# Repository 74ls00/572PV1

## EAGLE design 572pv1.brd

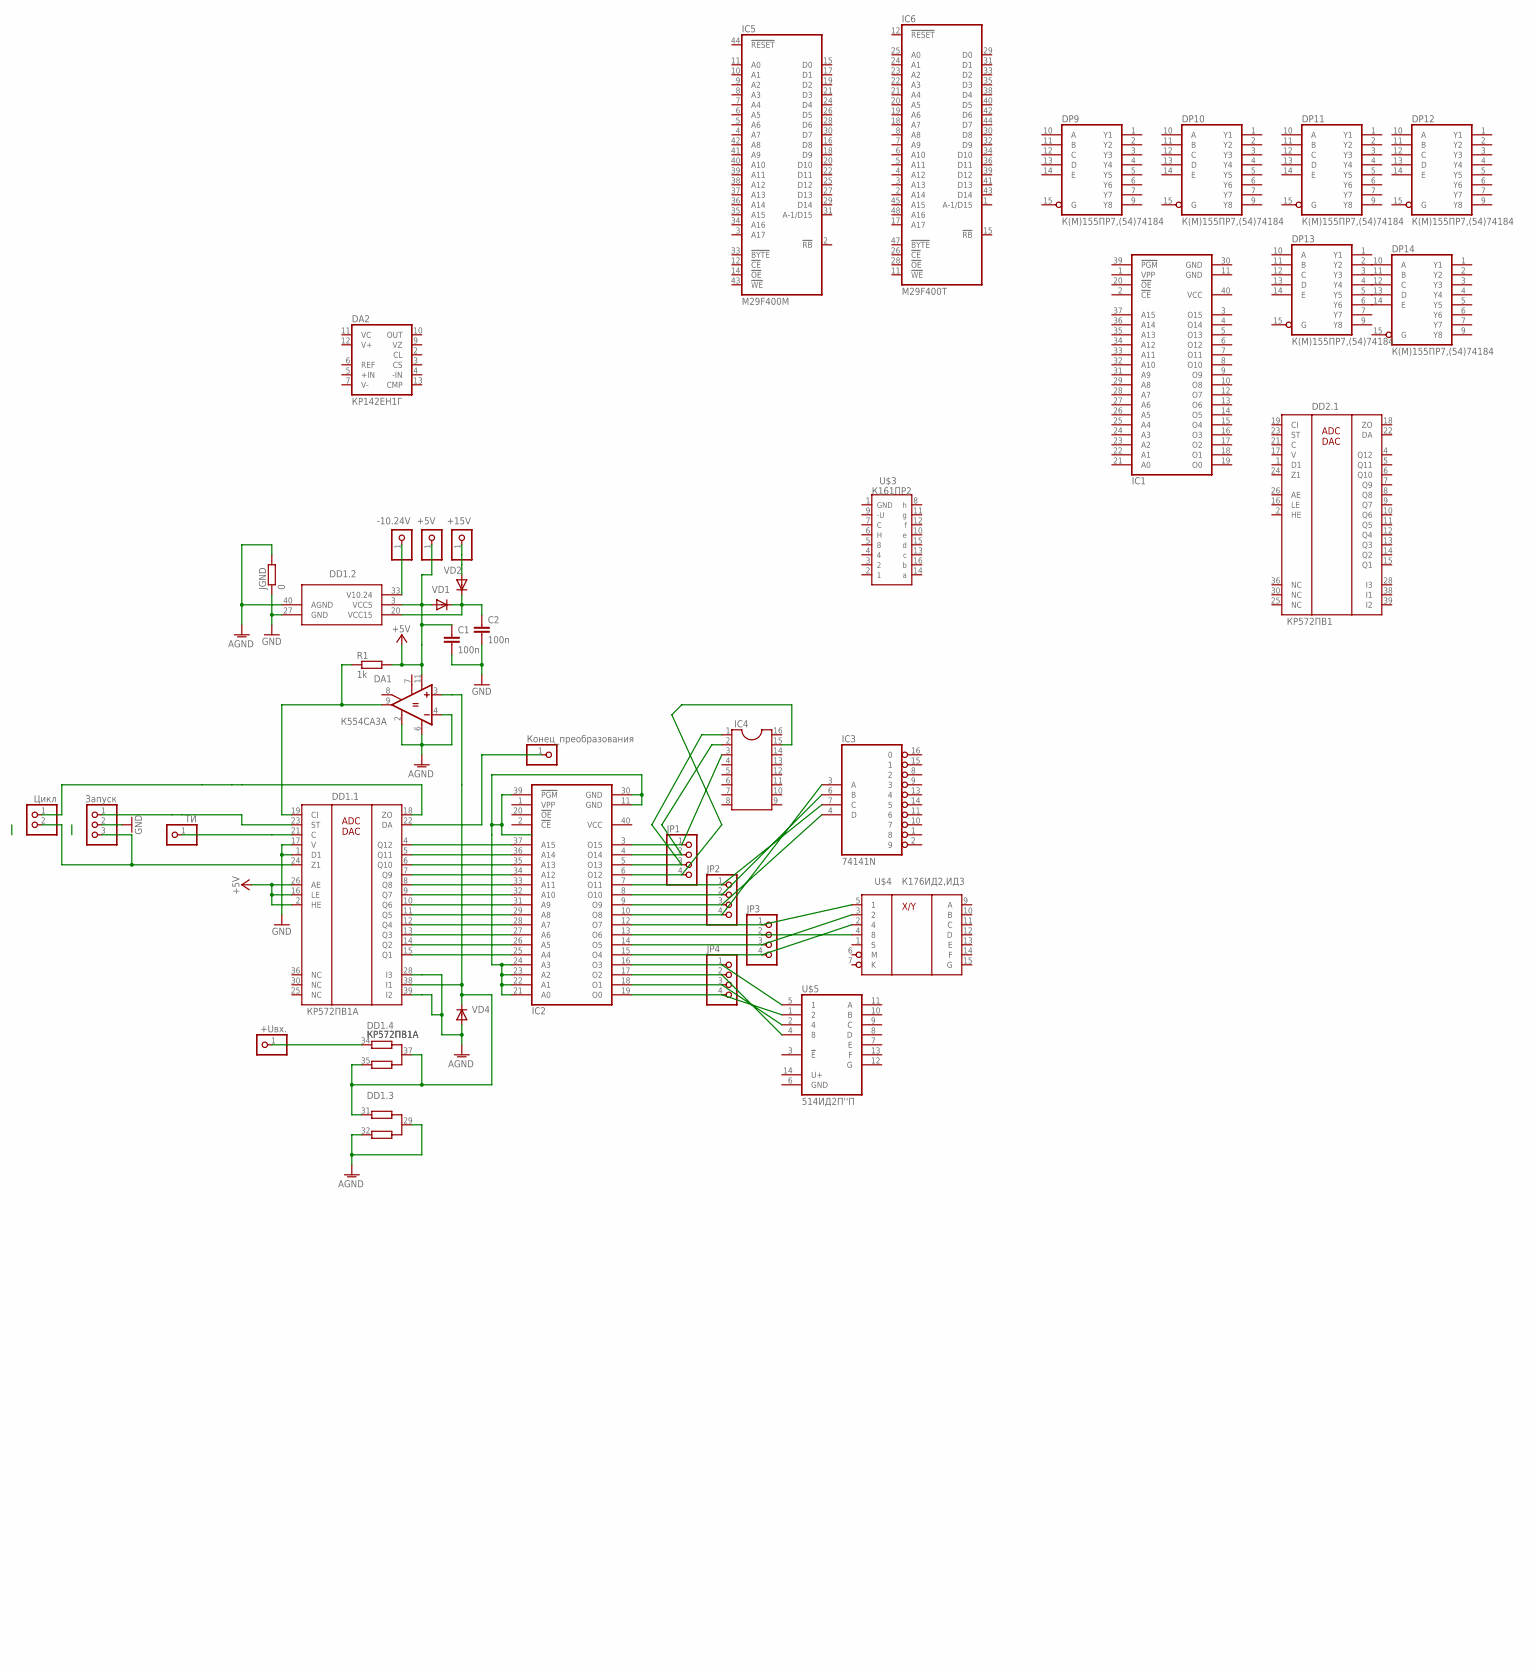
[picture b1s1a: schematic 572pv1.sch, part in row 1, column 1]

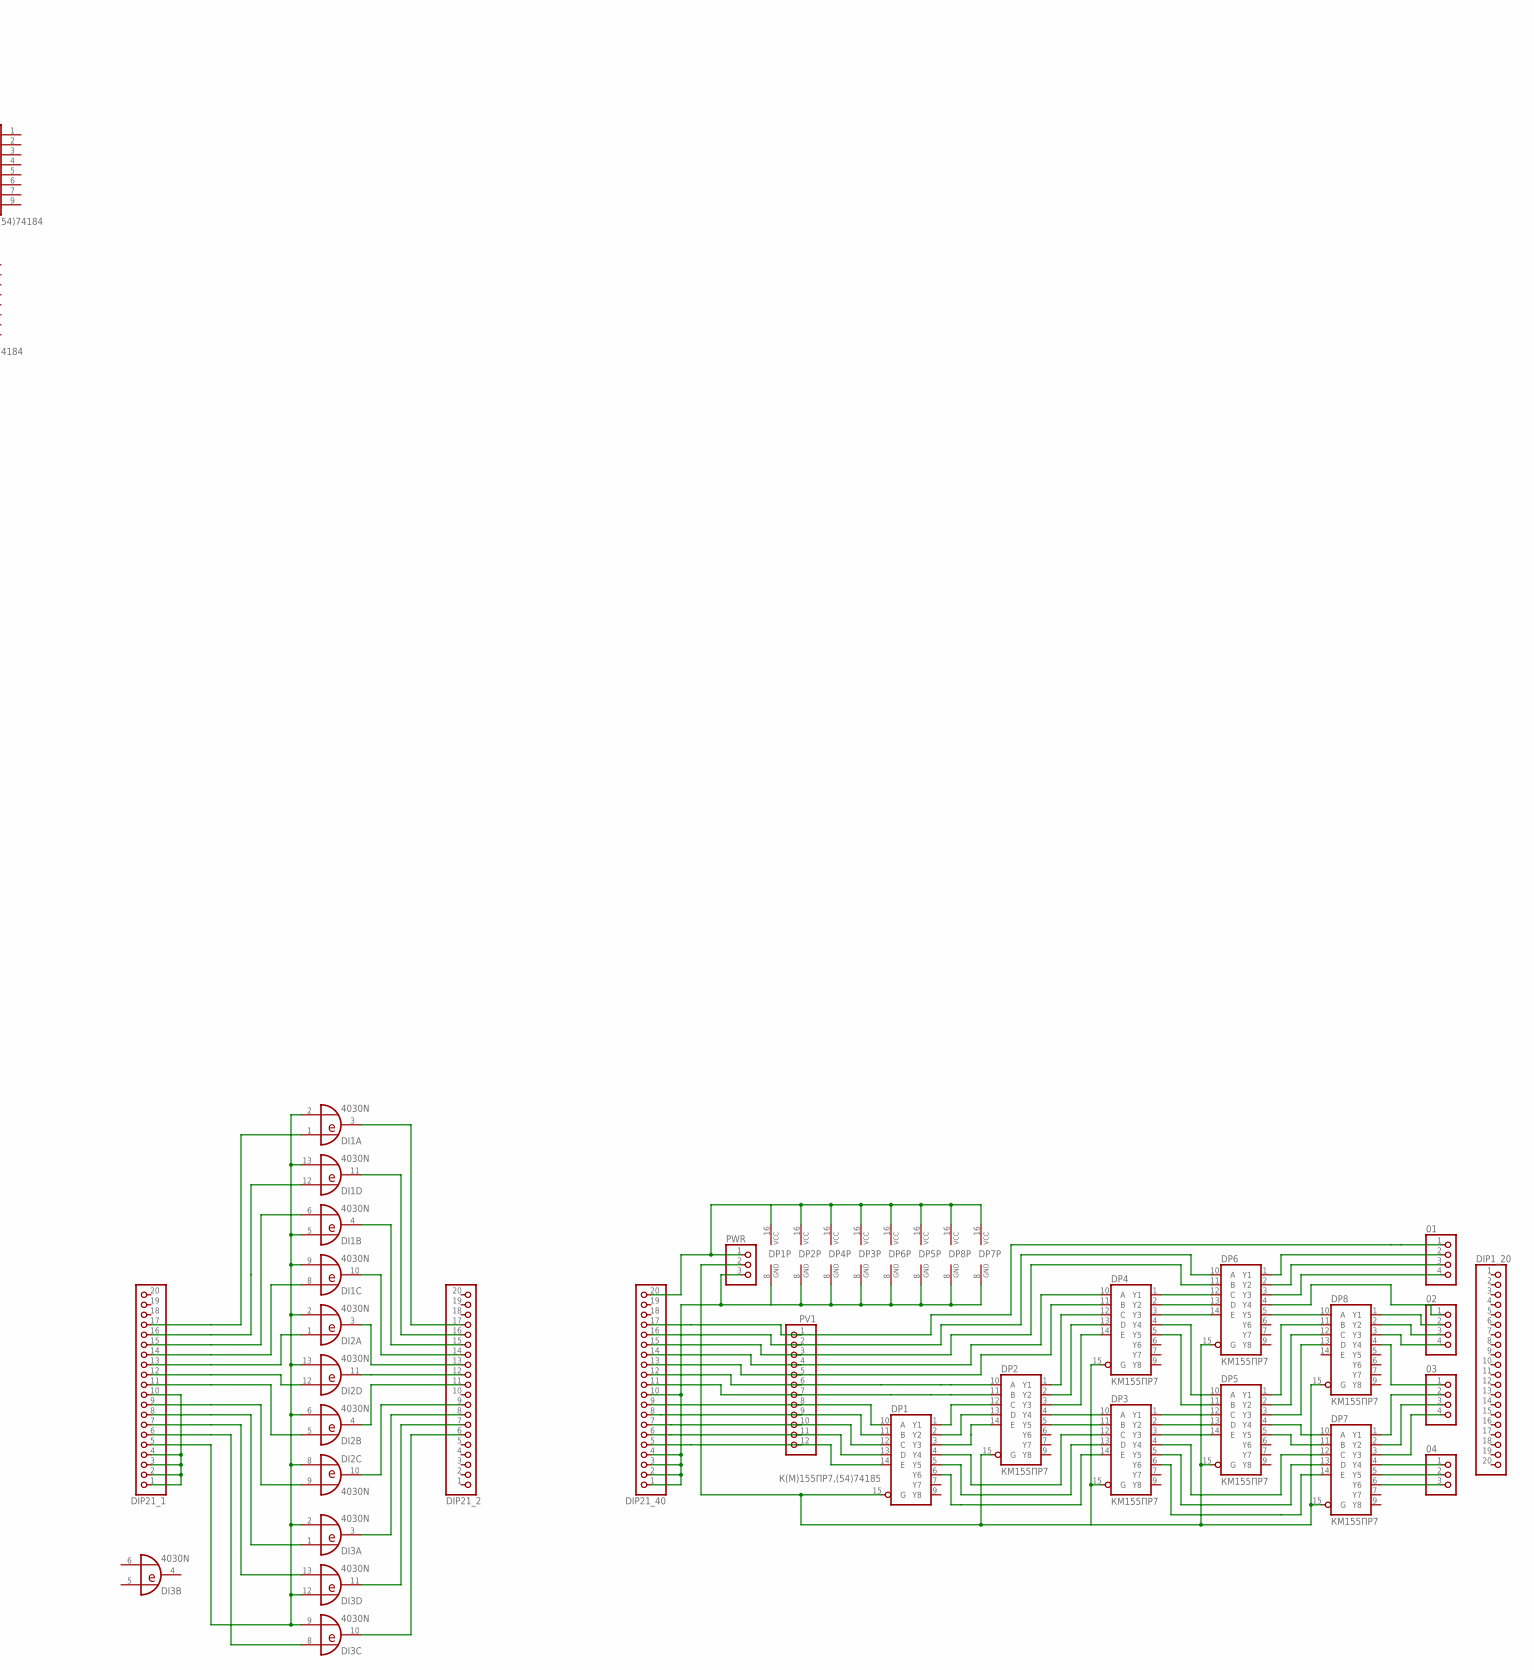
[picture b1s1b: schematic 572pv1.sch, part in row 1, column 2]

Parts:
01, 02, 03: PINHD-1X4; 1X04
04: PINHD-1X3; 1X03
+5V, +15V: PINHD-1X1; 1X01
+Uвх.: PINHD-1X1; 1X01
-10.24V: PINHD-1X1; 1X01
C1, C2: 100n; C0805
DA1: К554СА3А; DIL14
DA2: КР142ЕН1Г; DIL14
DD1: КР572ПВ1А; DIL40
DD2: КР572ПВ1; DIL40
DI1, DI2, DI3: 4030N; DIL14
DIP1_20, DIP21_1, DIP21_2, DIP21_40: PINHD-1X20; 1X20
DP1: К(М)155ПР7,(54)74185; DIL16
DP2, DP3, DP4, DP5, DP6, DP7, DP8: КМ155ПР7; DIL16
DP9, DP10, DP11, DP12, DP13, DP14: К(М)155ПР7,(54)74184; DIL16
IC1, IC2: 27210; DIL40
IC3: 74141N; DIL16
IC4: DIL16
IC5: M29F400M; SO44
IC6: M29F400T; TSOP48
JGND: 0; R0805
JP1, JP2, JP3, JP4: PINHD-1X4; 1X04
PV1: PINHD-1X12; 1X12
PWR: PINHD-1X3; 1X03
R1: 1k; R0805
U$3: К161ПР2; 238.16-1
U$4: К176ИД2,ИД3; DIL16B
U$5: 514ИД2П''П; 238.14-1
VD1, VD2, VD4: DIODE-SOD80C; SOD80C
Запуск: PINHD-1X3; 1X03
Конец_преобразования: PINHD-1X1; 1X01
ТИ: PINHD-1X1; 1X01
Цикл: PINHD-1X2/2; 1X02

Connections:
+5V: +5V.1, C1.1, DA1.11 (V+), DD1.2 (HE), DD1.3 (VCC5), DD1.16 (LE), DD1.26 (AE), R1.2, VD1.A
-VCC: U$3.9 (-VCC)
AGND: DA1.2 (GND), DA1.4 (-IN), DA1.6 (V-), DD1.28 (I3), DD1.29 (R2), DD1.32 (R1B), DD1.39 (I2), DD1.40 (AGND), DD2.40 (AGND), JGND.2, VD4.A
GND: C1.2, C2.2, DD1.1 (D1), DD1.17 (V), DD1.27 (GND), DD2.27 (GND), DP9.8 (GND), DP10.8 (GND), DP11.8 (GND), DP12.8 (GND), DP13.8 (GND), DP14.8 (GND), IC1.11 (GND), IC1.30 (GND), IC3.12 (GND), IC5.13 (GND), IC5.32 (GND), IC6.27 (GND), IC6.46 (GND), JGND.1, U$3.1 (GND), U$4.8 (GND), Запуск.2
unnamed: IC2.11 (GND), IC2.21 (A0), IC2.22 (A1), IC2.23 (A2), IC2.24 (A3), IC2.30 (GND), IC2.39 (!PGM)
unnamed: DD1.4 (Q12), IC2.37 (A15)
unnamed: C2.1, DD1.20 (VCC15), VD1.C, VD2.C
unnamed: DD1.5 (Q11), IC2.36 (A14)
unnamed: DD1.6 (Q10), IC2.35 (A13)
unnamed: DA1.3 (+IN), DD1.31 (R1A), DD1.35 (R1B), DD1.37 (R2), DD1.38 (I1), VD4.C
unnamed: DD1.7 (Q9), IC2.34 (A12)
unnamed: DD1.8 (Q8), IC2.33 (A11)
unnamed: DD1.9 (Q7), IC2.32 (A10)
unnamed: DD1.10 (Q6), IC2.31 (A9)
unnamed: DD1.11 (Q5), IC2.29 (A8)
unnamed: DD1.12 (Q4), IC2.28 (A7)
unnamed: DD1.13 (Q3), IC2.27 (A6)
unnamed: DD1.14 (Q2), IC2.26 (A5)
unnamed: DD1.15 (Q1), IC2.25 (A4)
unnamed: DIP21_40.9, DP1.10 (A), PV1.8
unnamed: DP13.2 (Y2), DP14.10 (A)
unnamed: IC2.4 (O14), IC4.2, JP1.2
unnamed: IC2.3 (O15), IC4.3, JP1.1
unnamed: +Uвх..1, DD1.34 (R1A)
unnamed: IC2.7 (O11), IC3.7 (C), JP2.1
unnamed: IC2.8 (O10), IC3.6 (B), JP2.2
unnamed: IC2.9 (O9), IC3.4 (D), JP2.3
unnamed: IC2.10 (O8), IC3.3 (A), JP2.4
unnamed: IC2.12 (O7), JP3.1, U$4.5 (1)
unnamed: IC2.13 (O6), JP3.2, U$4.4 (8)
unnamed: IC2.14 (O5), JP3.3, U$4.3 (2)
unnamed: IC2.15 (O4), JP3.4, U$4.2 (4)
unnamed: IC2.16 (O3), JP4.1, U$5.5 (1)
unnamed: IC2.17 (O2), JP4.2, U$5.4 (8)
unnamed: IC2.18 (O1), JP4.3, U$5.2 (4)
unnamed: IC2.19 (O0), JP4.4, U$5.1 (2)
unnamed: DIP21_40.8, DP1.11 (B), PV1.9
unnamed: DIP21_40.7, DP1.12 (C), PV1.10
unnamed: DIP21_40.6, DP1.13 (D), PV1.11
unnamed: DIP21_40.5, DP1.14 (E), PV1.12
unnamed: DP1.1 (Y1), DP2.12 (C)
unnamed: DP1.2 (Y2), DP2.13 (D)
unnamed: DP1.3 (Y3), DP2.14 (E)
unnamed: DIP21_40.11, DP2.11 (B), PV1.7
unnamed: DIP21_40.12, DP2.10 (A), PV1.6
unnamed: DP2.4 (Y4), DP3.10 (A)
unnamed: DP2.5 (Y5), DP3.11 (B)
unnamed: DP1.4 (Y4), DP3.12 (C)
unnamed: DP1.5 (Y5), DP3.13 (D)
unnamed: DP1.6 (Y6), DP3.14 (E)
unnamed: DP2.3 (Y3), DP4.14 (E)
unnamed: DP2.2 (Y2), DP4.13 (D)
unnamed: DP2.1 (Y1), DP4.12 (C)
unnamed: DIP21_40.13, DP4.11 (B), PV1.5
unnamed: DIP21_40.14, DP4.10 (A), PV1.4
unnamed: DP3.1 (Y1), DP5.12 (C)
unnamed: DP3.2 (Y2), DP5.13 (D)
unnamed: DP3.3 (Y3), DP5.14 (E)
unnamed: DP4.5 (Y5), DP5.11 (B)
unnamed: DP4.4 (Y4), DP5.10 (A)
unnamed: DP4.3 (Y3), DP6.14 (E)
unnamed: DP4.2 (Y2), DP6.13 (D)
unnamed: DP4.1 (Y1), DP6.12 (C)
unnamed: DP3.4 (Y4), DP7.12 (C)
unnamed: DP3.5 (Y5), DP7.13 (D)
unnamed: DP3.6 (Y6), DP7.14 (E)
unnamed: DP5.3 (Y3), DP8.13 (D)
unnamed: DP5.5 (Y5), DP7.11 (B)
unnamed: DP5.4 (Y4), DP7.10 (A)
unnamed: DP5.1 (Y1), DP8.11 (B)
unnamed: DP5.2 (Y2), DP8.12 (C)
unnamed: DP6.5 (Y5), DP8.10 (A)
unnamed: 04.1, DP7.4 (Y4)
unnamed: 04.2, DP7.5 (Y5)
unnamed: 04.3, DP7.6 (Y6)
unnamed: 03.2, DP7.1 (Y1)
unnamed: 03.3, DP7.2 (Y2)
unnamed: 03.4, DP7.3 (Y3)
unnamed: 03.1, DP8.4 (Y4)
unnamed: 02.3, DP8.2 (Y2)
unnamed: 02.2, DP8.1 (Y1)
unnamed: 02.4, DP8.3 (Y3)
unnamed: DIP21_40.15, DP6.11 (B), PV1.3
unnamed: DIP21_40.16, DP6.10 (A), PV1.2
unnamed: 01.1, DIP21_40.17, PV1.1
unnamed: 02.1, DP6.4 (Y4)
unnamed: 01.4, DP6.3 (Y3)
unnamed: 01.3, DP6.2 (Y2)
unnamed: 01.2, DP6.1 (Y1)
unnamed: DIP21_40.1, DIP21_40.2, DIP21_40.3, DIP21_40.4, DIP21_40.10, DP1.8 (GND), DP2.8 (GND), DP3.8 (GND), DP4.8 (GND), DP5.8 (GND), DP6.8 (GND), DP7.8 (GND), DP8.8 (GND), PWR.3
unnamed: DP1.15 (G), DP2.15 (G), DP3.15 (G), DP4.15 (G), DP5.15 (G), DP6.15 (G), DP7.15 (G), DP8.15 (G), PWR.2
unnamed: -10.24V.1, DD1.33 (V10.24)
unnamed: IC2.6 (O12), IC4.15, JP1.4
unnamed: DIP21_40.20, DP1.16 (VCC), DP2.16 (VCC), DP3.16 (VCC), DP4.16 (VCC), DP5.16 (VCC), DP6.16 (VCC), DP7.16 (VCC), DP8.16 (VCC), PWR.1
unnamed: IC2.5 (O13), IC4.1, JP1.3
unnamed: DD1.23 (ST), Запуск.1
unnamed: DA1.9 (OUT), DD1.19 (CI), R1.1
unnamed: DD1.21 (C), ТИ.1
unnamed: DD1.22 (DA), Конец_преобразования.1
unnamed: DP13.3 (Y3), DP14.11 (B)
unnamed: +15V.1, VD2.A
unnamed: DP13.4 (Y4), DP14.12 (C)
unnamed: DD1.24 (Z1), Запуск.3, Цикл.2
unnamed: DD1.18 (ZO), Цикл.1
unnamed: DP13.5 (Y5), DP14.13 (D)
unnamed: DP13.6 (Y6), DP14.14 (E)
unnamed: DI2.11 (O), DIP21_2.12
unnamed: DI2.12 (I0), DIP21_1.12
unnamed: DI2.5 (I0), DIP21_1.11
unnamed: DI1.8 (I0), DIP21_1.14
unnamed: DI1.6 (I1), DIP21_1.15
unnamed: DI1.12 (I0), DIP21_1.16
unnamed: DI1.1 (I0), DIP21_1.17
unnamed: DI2.9 (I1), DIP21_1.9
unnamed: DI3.1 (I0), DIP21_1.8
unnamed: DI3.13 (I1), DIP21_1.7
unnamed: DI3.8 (I0), DIP21_1.6
unnamed: DI2.3 (O), DIP21_2.13
unnamed: DI2.1 (I0), DIP21_1.13
unnamed: DIP21_1.1, DIP21_1.2, DIP21_1.3, DIP21_1.4, DIP21_1.10
unnamed: DI1.2 (I1), DI1.5 (I0), DI1.9 (I1), DI1.13 (I1), DI2.2 (I1), DI2.6 (I1), DI2.8 (I0), DI2.13 (I1), DI3.2 (I1), DI3.9 (I1), DI3.12 (I0), DIP21_1.5
unnamed: DI1.10 (O), DIP21_2.14
unnamed: DI1.4 (O), DIP21_2.15
unnamed: DI1.11 (O), DIP21_2.16
unnamed: DI1.3 (O), DIP21_2.17
unnamed: DI2.4 (O), DIP21_2.11
unnamed: DI2.10 (O), DIP21_2.9
unnamed: DI3.3 (O), DIP21_2.8
unnamed: DI3.11 (O), DIP21_2.7
unnamed: DI3.10 (O), DIP21_2.6
V10.24: DD2.33 (V10.24)
VCC: DP9.16 (VCC), DP10.16 (VCC), DP11.16 (VCC), DP12.16 (VCC), DP13.16 (VCC), DP14.16 (VCC), IC1.40 (VCC), IC2.40 (VCC), IC3.5 (VCC), IC5.23 (VCC), IC6.37 (VCC), U$4.16 (VCC)
VCC5: DD2.3 (VCC5)
VCC15: DD2.20 (VCC15)
VDD: DI1.14 (VDD), DI2.14 (VDD), DI3.14 (VDD)
VSS: DI1.7 (VSS), DI2.7 (VSS), DI3.7 (VSS)

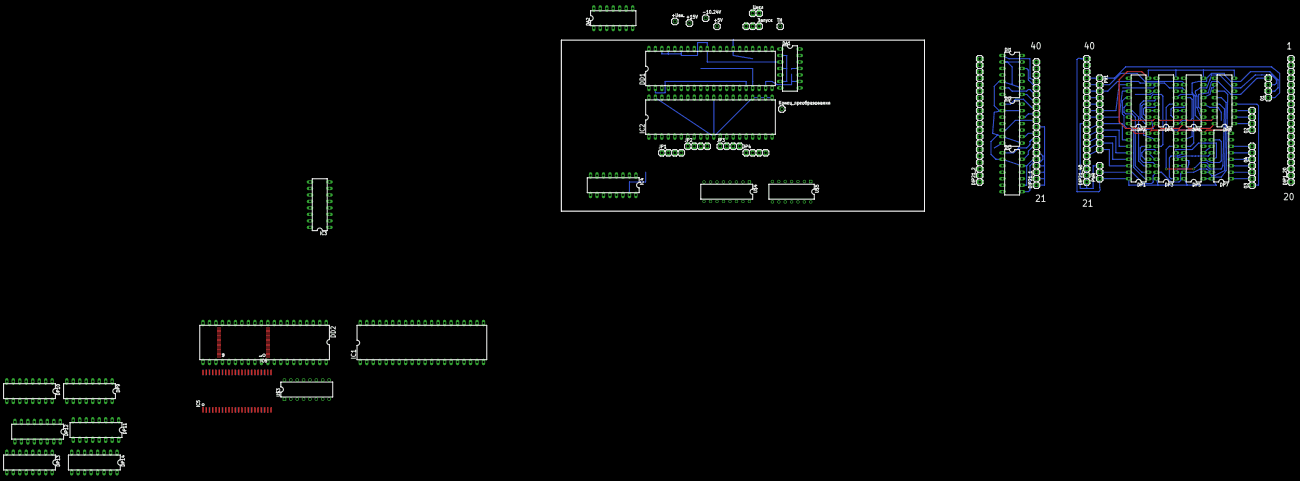
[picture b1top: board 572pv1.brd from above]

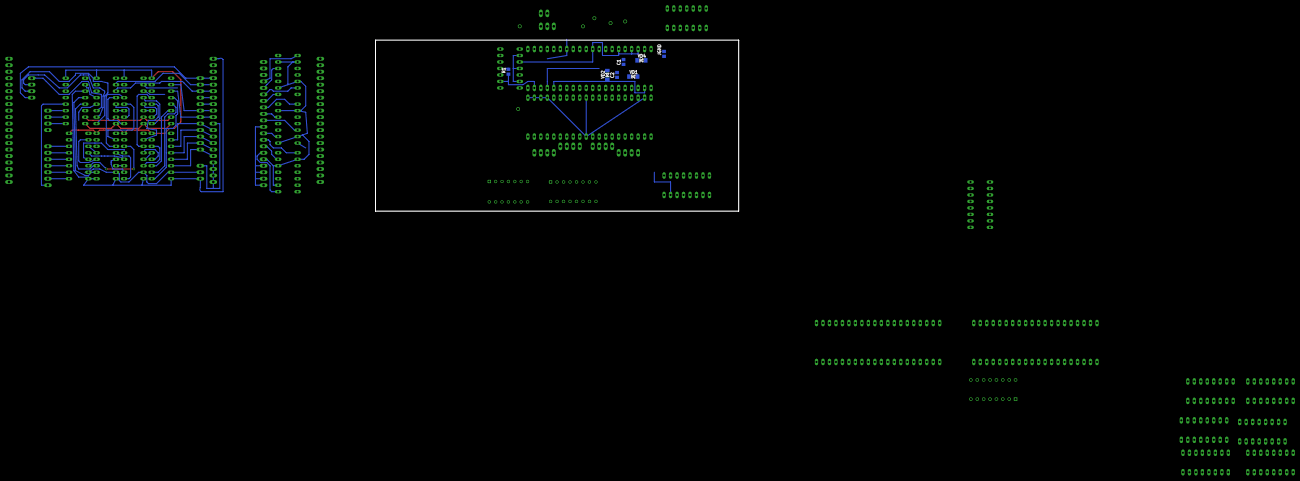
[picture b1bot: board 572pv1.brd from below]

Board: 2 copper layers, 142.2 x 67.0 mm, 59 parts (7 on the bottom side), 132 nets.
